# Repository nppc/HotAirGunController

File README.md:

# HotAirGunController
## Controller for Hot Air Gun with 220v heater and 24v fan
You can use Hot Air Desoldering Gun Handle FOR 858 858D 898D 852D Soldering Station Hot-air Rework Station

Arduino Nano

i2c OLED 0.91'' (128x32 pixels)

and any 240AC Solid State Switch like CPC1998

PCB from oshpark: https://oshpark.com/shared_projects/ofOX8gMQ

## Workable PIDs
P: 60

I: 3

D: 100

## Alternative PIDs
If your PID control goes crazy, then try these PIDs:

P: 40

I: 3

D: 30

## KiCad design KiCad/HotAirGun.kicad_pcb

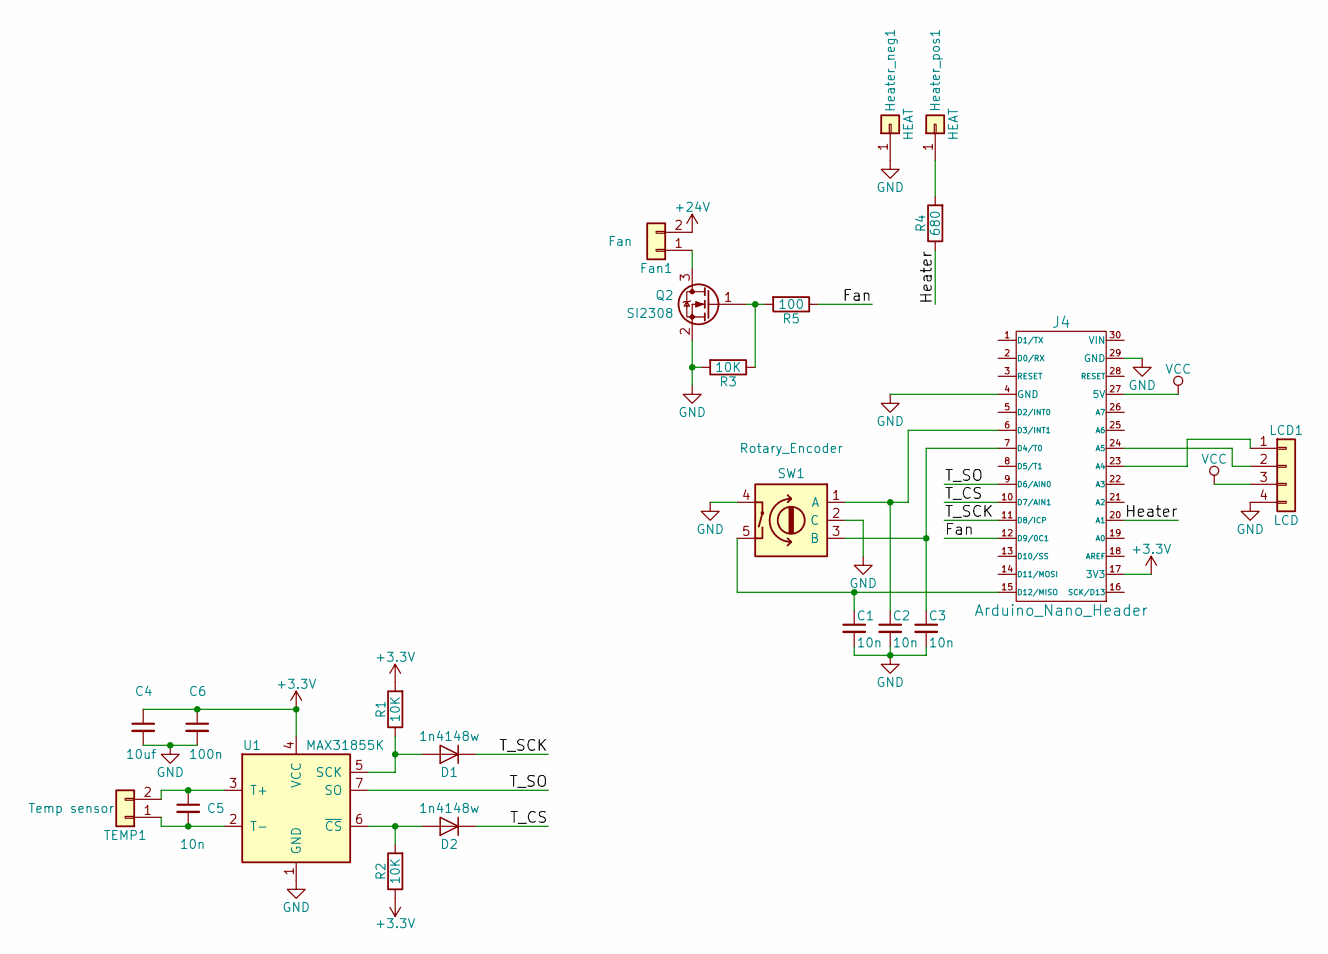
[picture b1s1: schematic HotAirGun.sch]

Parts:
C1, C2, C3, C5: 10n; C_0603
C4: 10uf; C_0603
C6: 100n; C_0603
D1, D2: 1n4148w; D_SOD-123F
Fan1: Fan; Pin_Header_Straight_1x02_Pitch2.54mm
Heater_neg1: HEAT; Pin_Header_Angled_1x01_Pitch2.54mm
Heater_pos1: HEAT; Pin_Header_Angled_1x01_Pitch2.54mm
J4: Arduino_Nano_Header; Arduino_Nano
LCD1: LCD; Pin_Header_Straight_1x04_Pitch2.54mm
Q2: SI2308; SOT-23
R1, R2, R3: 10K; R_0603
R4: 680; R_0603
R5: 100; R_0603
SW1: Rotary_Encoder; SF-ROTARY-ENCODER
TEMP1: Temp sensor; Pin_Header_Straight_1x02_Pitch2.54mm
U1: MAX31855K; SOIC-8_3.9x4.9mm_Pitch1.27mm

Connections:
+3V3: C4.1, C6.1, J4.17 (3V3), R1.2, R2.1, U1.4 (VCC)
/Fan: J4.12 (D9/0C1), R5.1
/Heater: J4.20 (A1), R4.1
/T_CS: D2.1 (K), J4.10 (D7/AIN1)
/T_SCK: D1.1 (K), J4.11 (D8/ICP)
/T_SO: J4.9 (D6/AIN0), U1.7 (SO)
GND: C1.2, C2.2, C3.2, C4.2, C6.2, Heater_neg1.1, J4.4 (GND), J4.29 (GND), LCD1.4, Q2.2 (S), R3.2, SW1.2 (C), SW1.4, U1.1 (GND)
unnamed: C1.1, J4.15 (D12/MISO), SW1.5
unnamed: C2.1, J4.6 (D3/INT1), SW1.1 (A)
unnamed: C3.1, J4.7 (D4/T0), SW1.3 (B)
unnamed: C5.1, TEMP1.2, U1.3 (T+)
unnamed: C5.2, TEMP1.1, U1.2 (T-)
unnamed: D1.2 (A), R1.1, U1.5 (SCK)
unnamed: D2.2 (A), R2.2, U1.6 (~CS~)
unnamed: Fan1.1, Q2.3 (D)
unnamed: Heater_pos1.1, R4.2
unnamed: J4.23 (A4), LCD1.1
unnamed: J4.24 (A5), LCD1.2
unnamed: Q2.1 (G), R3.1, R5.2
VCC: J4.27 (5V), LCD1.3

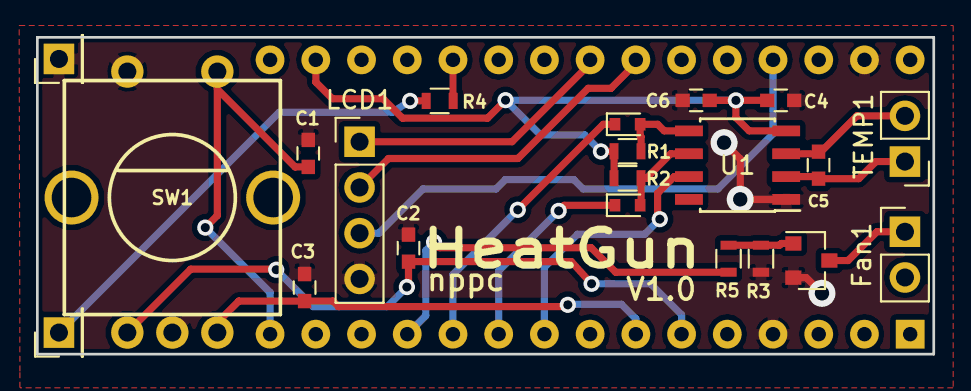
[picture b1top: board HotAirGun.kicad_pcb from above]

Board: 2 copper layers, 49.8 x 17.6 mm, 22 parts (1 on the bottom side), 20 nets.

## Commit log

2018-01-15 First test code
2018-01-15 Testing Heater element
2018-01-15 KiCad project created
2018-01-20 ThermoCouple controller Breakout board
2018-01-20 Add CNC project
2018-01-20 some gcode changes to CNC
2018-01-20 work in progress
2018-01-22 SCAD project.
2018-01-23 Draft of SCAD is ready
2018-01-24 continue work on firmware
2018-01-24 Changs
2018-01-25 Some alfa working firmware is ready for testing
2018-01-25 More or less stable version
2018-01-26 Adjusted PID scalling and other minor issues
2018-02-06 Some texts added
2018-02-06 SOD123 diodes
2018-02-06 Final adjustments
2018-02-06 Add conditionals for Prototype board and final PCB
2018-03-03 Led pin initialisation
2018-03-03 Cosmetic change enter config
2018-03-04 Safe Temperature added. Some improvements on Startup Fan control
2018-03-04 Highlight editable value
2018-03-04 Suspend logic
2018-03-04 Suspend working
2018-03-04 Suspend mode now is very simple
2018-03-05 Added support of magnet sensor at A3 pin
2018-03-05 Timer speed is left unchanged
2018-03-05 Add suspend indicator
2018-03-05 Adjusted position of the arrow
2018-03-05 Fix bug with config entering
2018-04-06 A bit faster temperature readings
2018-04-06 Added schematic and 3D model of PCB
2018-04-06 Image path fix
2018-05-14 BOM created
2018-05-14 added external components
2018-05-14 Added connection diagram
2018-05-14 Added hot air gun handle information
2021-08-16 fix compilation issue after adding max31855
2021-08-16 Add oled pic
2021-08-16 Add more info
2021-08-16 Added link to PCB
